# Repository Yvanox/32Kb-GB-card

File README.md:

# 32Kb-GB-card
This is my version of the 32Kb game card for the GB, it uses the SST39SF040 memory.

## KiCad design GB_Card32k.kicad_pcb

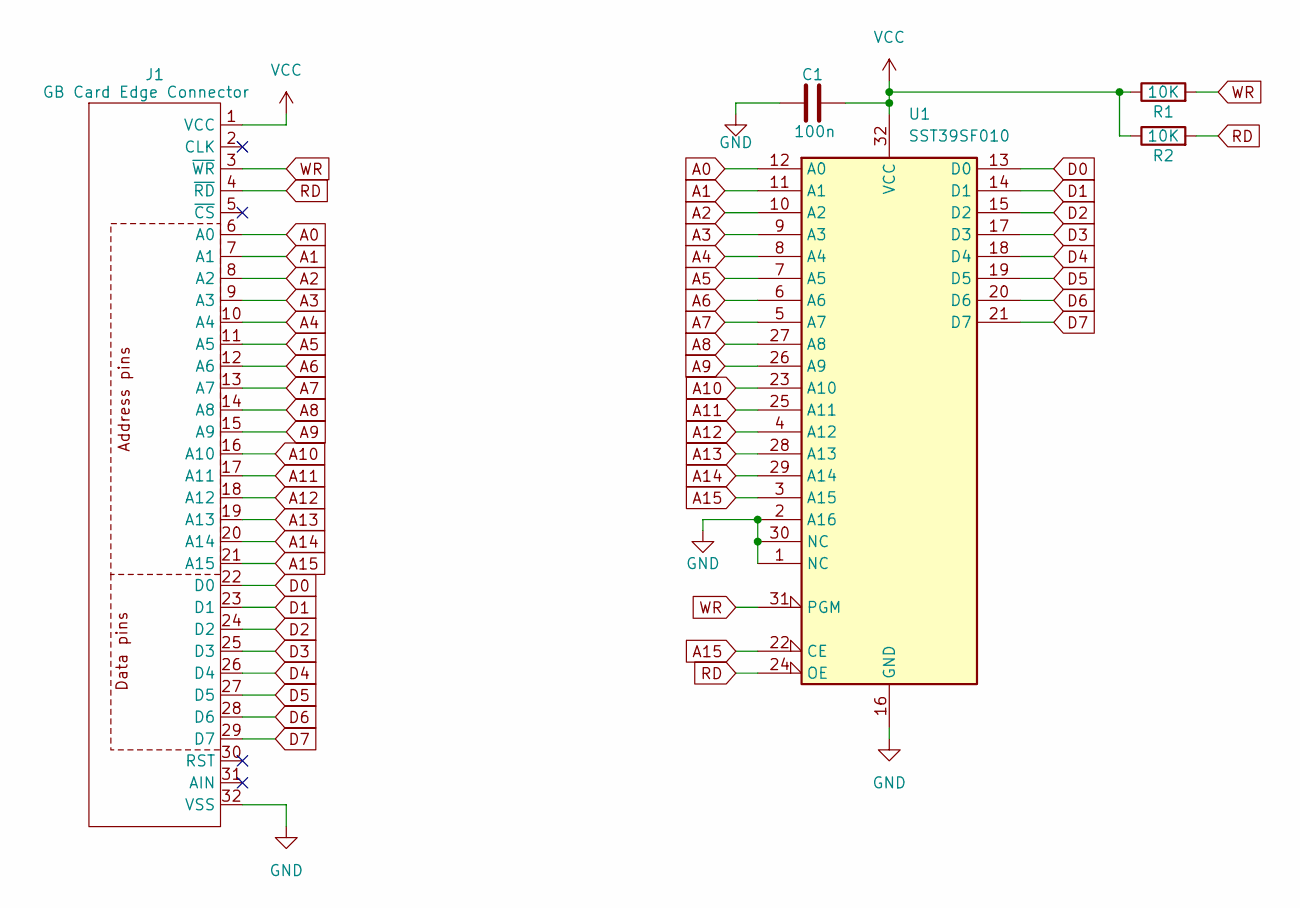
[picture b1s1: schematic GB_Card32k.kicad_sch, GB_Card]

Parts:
C1: 100n; C_0603_1608Metric_Pad1.08x0.95mm_HandSolder
J1: GB Card Edge Connector; GB_Edge_Conn
R1, R2: 10K; R_0603_1608Metric_Pad0.98x0.95mm_HandSolder
U1: SST39SF010; PLCC-32_11.4x14.0mm_P1.27mm

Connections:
A0: J1.6 (A0), U1.12 (A0)
A1: J1.7 (A1), U1.11 (A1)
A2: J1.8 (A2), U1.10 (A2)
A3: J1.9 (A3), U1.9 (A3)
A4: J1.10 (A4), U1.8 (A4)
A5: J1.11 (A5), U1.7 (A5)
A6: J1.12 (A6), U1.6 (A6)
A7: J1.13 (A7), U1.5 (A7)
A8: J1.14 (A8), U1.27 (A8)
A9: J1.15 (A9), U1.26 (A9)
A10: J1.16 (A10), U1.23 (A10)
A11: J1.17 (A11), U1.25 (A11)
A12: J1.18 (A12), U1.4 (A12)
A13: J1.19 (A13), U1.28 (A13)
A14: J1.20 (A14), U1.29 (A14)
A15: J1.21 (A15), U1.3 (A15), U1.22 (CE)
D0: J1.22 (D0), U1.13 (D0)
D1: J1.23 (D1), U1.14 (D1)
D2: J1.24 (D2), U1.15 (D2)
D3: J1.25 (D3), U1.17 (D3)
D4: J1.26 (D4), U1.18 (D4)
D5: J1.27 (D5), U1.19 (D5)
D6: J1.28 (D6), U1.20 (D6)
D7: J1.29 (D7), U1.21 (D7)
GND: C1.1, J1.32 (VSS), U1.1 (NC), U1.2 (A16), U1.16 (GND), U1.30 (NC)
RD: J1.4 (~RD), R2.2, U1.24 (OE)
VCC: C1.2, J1.1 (VCC), R1.1, R2.1, U1.32 (VCC)
WR: J1.3 (~WR), R1.2, U1.31 (PGM)

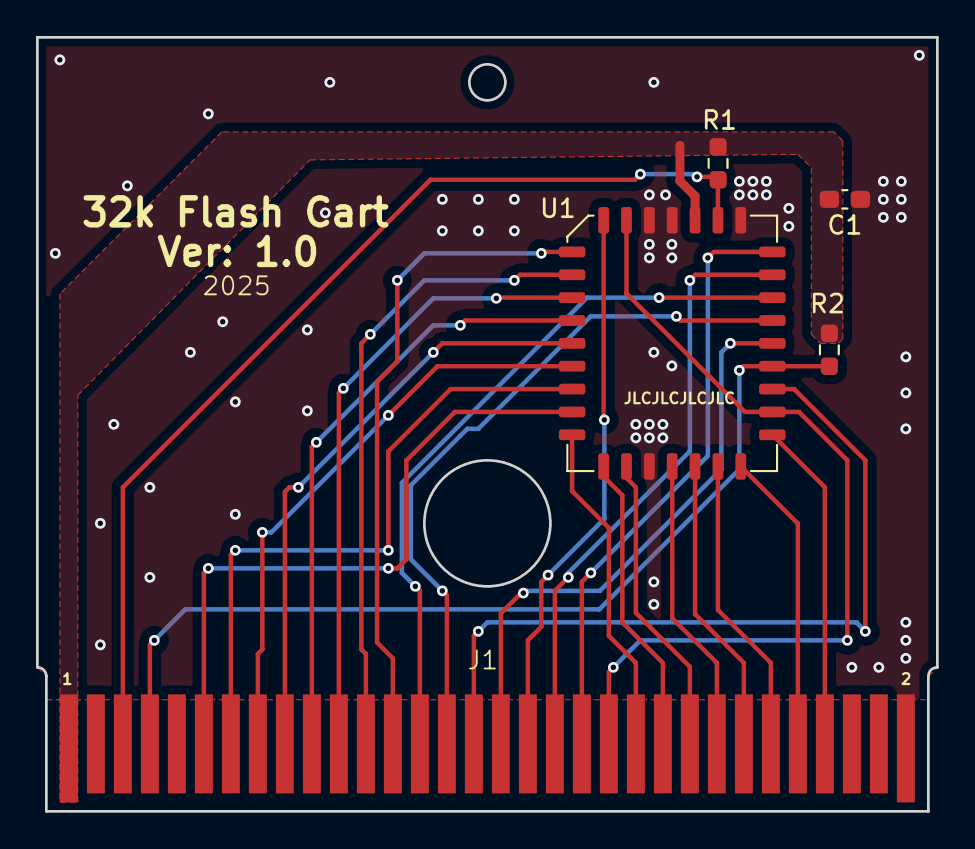
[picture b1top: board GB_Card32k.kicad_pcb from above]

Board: 2 copper layers, 50.0 x 43.0 mm, 5 parts (0 on the bottom side), 28 nets.

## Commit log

2025-06-24 Created git project
